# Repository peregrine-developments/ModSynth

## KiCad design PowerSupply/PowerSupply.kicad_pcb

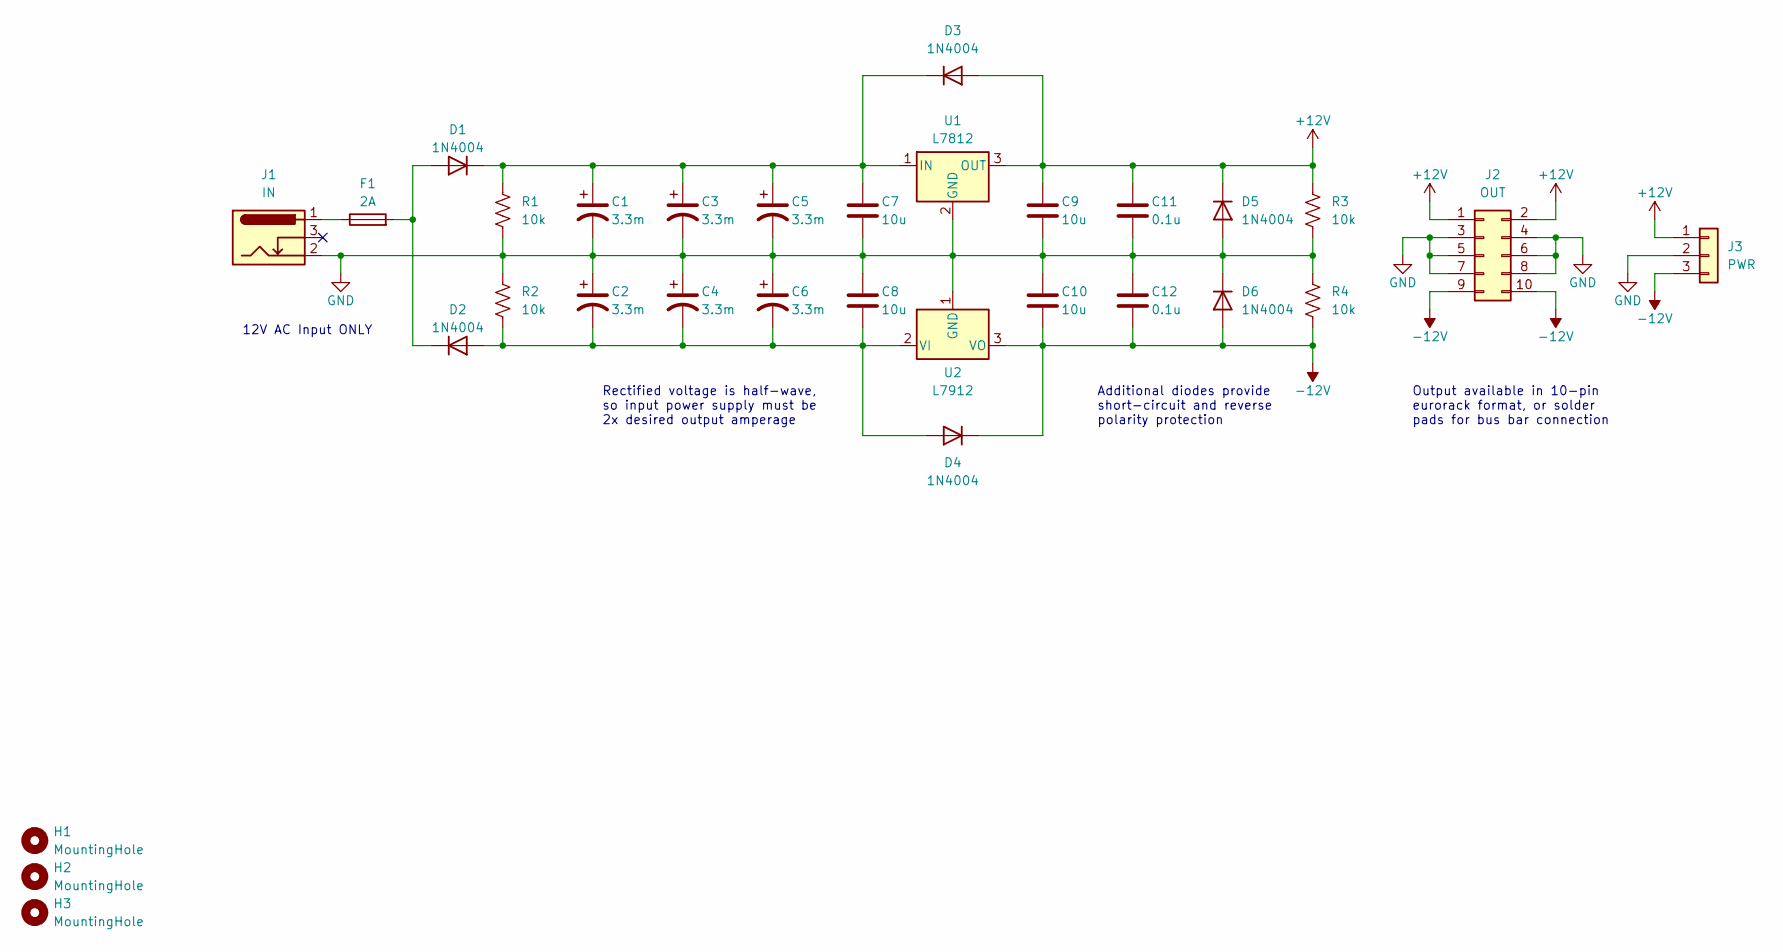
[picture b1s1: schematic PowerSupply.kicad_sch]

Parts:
C1, C2, C3, C4, C5, C6: 3.3m; CP_Radial_D16.0mm_P7.50mm
C7, C8, C9, C10: 10u; C_Rect_L7.0mm_W4.5mm_P5.00mm
C11, C12: 0.1u; C_Rect_L4.0mm_W2.5mm_P2.50mm
D1, D2, D3, D4, D5, D6: 1N4004; D_DO-41_SOD81_P7.62mm_Horizontal
F1: 2A; Fuseholder_Cylinder-5x20mm_Schurter_0031_8201_Horizontal_Op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
H1, H2, H3: MountingHole; MountingHole_4.3mm_M4
J1: IN; BarrelJack_GCT_DCJ200-10-A_Horizontal
J2: OUT; IDC-Header_2x05_P2.54mm_Vertical
J3: PWR; SolderWire-0.75sqmm_1x03_P7mm_D1.25mm_OD3.5mm
R1, R2, R3, R4: 10k; R_Axial_DIN0204_L3.6mm_D1.6mm_P5.08mm_Horizontal
U1: L7812; TO-220-3_Horizontal_TabDown
U2: L7912; TO-220-3_Horizontal_TabDown

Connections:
+12V: C9.1, C11.1, D3.2 (A), D5.1 (K), J2.1, J2.2, J3.1, R3.1, U1.3 (OUT)
-12V: C10.2, C12.2, D4.1 (K), D6.2 (A), J2.9, J2.10, J3.3, R4.2, U2.3 (VO)
GND: C1.2, C2.1, C3.2, C4.1, C5.2, C6.1, C7.2, C8.1, C9.2, C10.1, C11.2, C12.1, D5.2 (A), D6.1 (K), J1.2, J2.3, J2.4, J2.5, J2.6, J2.7, J2.8, J3.2, R1.2, R2.1, R3.2, R4.1, U1.2 (GND), U2.1 (GND)
unnamed: C1.1, C3.1, C5.1, C7.1, D1.1 (K), D3.1 (K), R1.1, U1.1 (IN)
unnamed: C2.2, C4.2, C6.2, C8.2, D2.2 (A), D4.2 (A), R2.2, U2.2 (VI)
unnamed: D1.2 (A), D2.1 (K), F1.2
unnamed: F1.1, J1.1

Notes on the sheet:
Rectified voltage is half-wave, so input power supply must be 2x desired output amperage
Additional diodes provide short-circuit and reverse polarity protection
Output available in 10-pin eurorack format, or solder pads for bus bar connection
12V AC Input ONLY

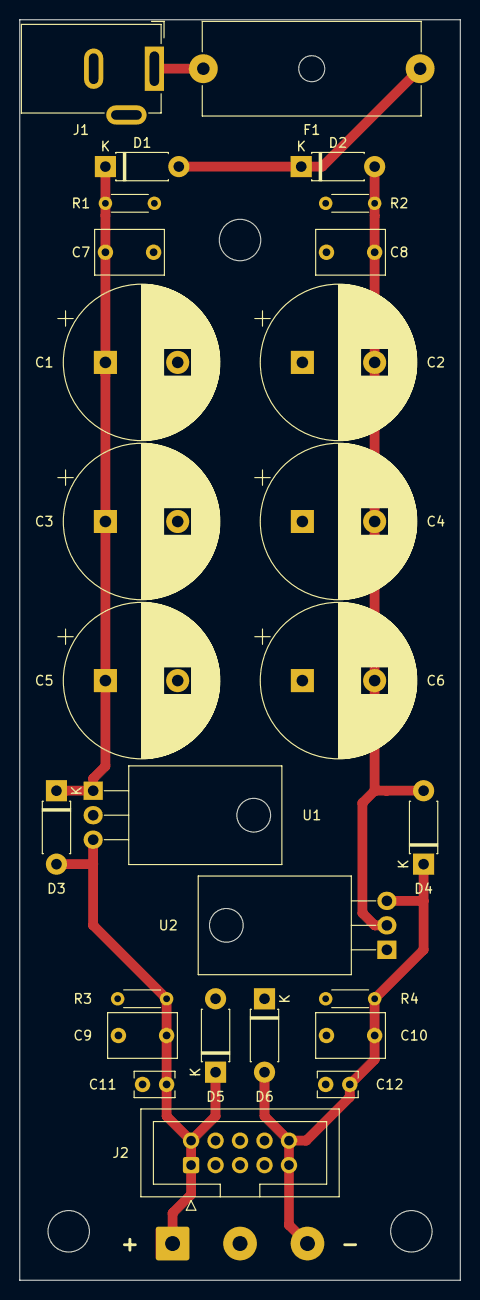
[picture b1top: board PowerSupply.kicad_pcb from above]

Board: 2 copper layers, 45.7 x 130.8 mm, 31 parts (0 on the bottom side), 7 nets.

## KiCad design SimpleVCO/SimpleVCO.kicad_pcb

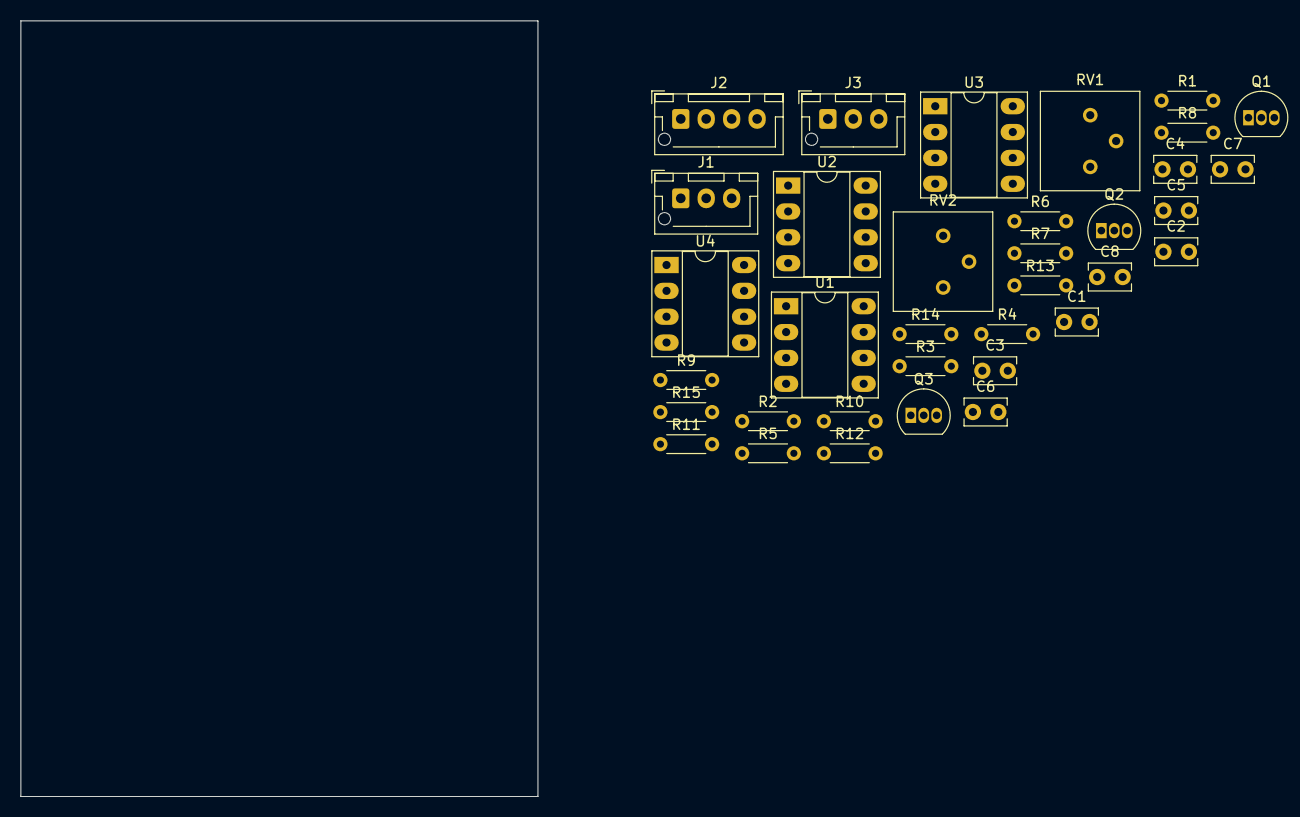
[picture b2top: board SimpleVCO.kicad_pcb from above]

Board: 2 copper layers, 50.8 x 76.2 mm, 35 parts (0 on the bottom side), 24 nets, no tracks yet.

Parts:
C1: 1n; C_Rect_L4.0mm_W2.5mm_P2.50mm
C2: ~4n; C_Rect_L4.0mm_W2.5mm_P2.50mm
C3, C4, C5, C6, C7, C8: 0.1u; C_Rect_L4.0mm_W2.5mm_P2.50mm
J1: PWR; JST_XH_B3B-XH-AM_1x03_P2.50mm_Vertical
J2: CV; JST_XH_B4B-XH-AM_1x04_P2.50mm_Vertical
J3: SIG; JST_XH_B3B-XH-AM_1x03_P2.50mm_Vertical
Q1, Q2, Q3: BC548; TO-92_Inline
R1, R2, R3, R7, R8, R9, R14, R15: 100k; R_Axial_DIN0204_L3.6mm_D1.6mm_P5.08mm_Horizontal
R4: 1M; R_Axial_DIN0204_L3.6mm_D1.6mm_P5.08mm_Horizontal
R5: 1k; R_Axial_DIN0204_L3.6mm_D1.6mm_P5.08mm_Horizontal
R6: 22k; R_Axial_DIN0204_L3.6mm_D1.6mm_P5.08mm_Horizontal
R10, R11, R12, R13: 56k; R_Axial_DIN0204_L3.6mm_D1.6mm_P5.08mm_Horizontal
RV1, RV2: 10k; Potentiometer_Bourns_3386P_Vertical
U1, U2, U3, U4: LM358; DIP-8_W7.62mm_Socket_LongPads

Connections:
+5V: C3.1, C4.1, C7.1, C8.1, J1.1, R4.1, R7.1, U1.8 (V+), U2.8 (V+), U3.8 (V+), U4.8 (V+)
-5V: C5.1, C6.1, J1.2, U1.4 (V-), U2.4 (V-)
/KEY: J2.1, R1.1
/LFO: J2.3, R3.1
/SQR: J3.2, U4.6 (-), U4.7
/TRI: J3.1, U4.1, U4.2 (-)
/TUNE: J2.2, R2.1
/VEXPO: R9.1, R10.1, RV2.3, U1.1
/VIN: Q1.2 (B), RV1.2, RV1.3, U1.7
/VREF: R7.2, R8.1, R13.2
GND: C3.2, C4.2, C5.2, C6.2, C7.2, C8.2, J1.3, J2.4, J3.3, Q2.2 (B), Q3.3 (E), R8.2, R11.1, U1.2 (-), U1.5 (+), U2.2 (-), U2.3 (+), U2.6 (-), U3.4 (V-), U4.4 (V-)
unnamed: C1.1, Q1.1 (C), R4.2, U2.5 (+)
unnamed: C1.2, R5.2, U2.7
unnamed: C2.1, R9.2, R12.2, U3.2 (-)
unnamed: C2.2, U3.1, U3.6 (-), U4.3 (+)
unnamed: Q1.3 (E), Q2.3 (E), R5.1
unnamed: Q2.1 (C), R6.1, U1.3 (+)
unnamed: Q3.1 (C), R12.1
unnamed: Q3.2 (B), R15.2
unnamed: R1.2, R2.2, R3.2, RV1.1, U1.6 (-)
unnamed: R6.2, RV2.1, RV2.2
unnamed: R10.2, R11.2, U3.3 (+)
unnamed: R13.1, R14.2, U3.5 (+)
unnamed: R14.1, R15.1, U3.7, U4.5 (+)

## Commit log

2022-01-05 Initial upload
